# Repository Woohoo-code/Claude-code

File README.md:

# pcba-builder

A CLI that drives the [Claude Code](https://claude.com/claude-code) CLI
(`claude`) to turn a plain-language board description into a first-pass
PCBA (printed circuit board assembly) design package: a bill of materials,
a logical netlist, schematic block descriptions, PCB layout/manufacturing
notes, and assembly/bring-up instructions - plus, generated locally and
offline from that BOM:

- **KiCad export** - real `.kicad_mod` footprints and a placed (unrouted)
  `.kicad_pcb`, with every pin positioned and numbered from its package's
  physical shape and size (JEDEC/IPC-style: pin 1 marked, numbering
  counterclockwise around the body) - see `pinouts.md`.
- **GLB export** - a `.glb` 3D preview of the assembled board (board slab
  + one box per part, sized and placed to match the KiCad layout) you can
  open in any glTF viewer.
- **Online model search** - `pcba-builder models` uses `claude -p` with
  web search to look up a datasheet and, where one exists, a direct
  downloadable 3D/footprint file (STEP/IGES/WRL/GLB) for each part in the
  BOM, and fetches any direct links it finds.
- **Standalone executable** - `scripts/build_exe.sh` / `build_exe.bat`
  package the whole tool with PyInstaller into a single `pcba-builder`
  (or `pcba-builder.exe` on Windows) binary - no Python install needed to
  run it.

It does not draw a schematic or auto-route a board. `export-kicad`
produces a *placed but unrouted* starting point (no ratsnest - the
underlying netlist connectivity from `netlist.md` isn't wired into the
`.kicad_pcb` yet), and `models`/pin-labeling are geometry- and
search-driven, not a guarantee that a given part's silicon pinout matches
the physical positions generated. Always check a generated design against
the real datasheet before fabricating.

## Example boards

Complete, hand-finished design packages in this tool's format. Both are
**placed and fully routed** (0 DRC errors), with Gerbers, pick-and-place,
and a script that regenerates the board through KiCad 7's `pcbnew` API.
`export-kicad`, by contrast, only places parts on a grid.

- [`boards/cc1101-mini/`](boards/cc1101-mini/): an 18.5 x 12.6 mm 4-layer
  TI CC1101 433 MHz module with a U.FL connector.
- [`boards/nano-every-cc1101/`](boards/nano-every-cc1101/): a 70 x 45 mm
  **2-layer** Arduino Nano Every carrier with two CC1101s covering every
  CC1101 band. It has JLCPCB-assembled coil antennas for 315/433/868/915 MHz
  (plus optional SMA jacks), a level shifter, an LDO and a pin breakout.
  Freerouting autoroutes the non-RF nets.

## Requirements

- Python 3.9+ (only to run from source - the packaged executable needs nothing)
- The `claude` CLI installed and authenticated (`claude --version` should work),
  for `build`, `review`, and `models`
- Internet access (through your normal `claude` CLI setup) for `models`

## Install (from source)

```
pip install -e .
```

This installs a `pcba-builder` command. You can also run it directly with
`python -m pcba_builder.cli` from the repo root.

## Build a standalone executable

```
./scripts/build_exe.sh      # Linux/macOS -> dist/pcba-builder
scripts\build_exe.bat       # Windows     -> dist\pcba-builder.exe
```

PyInstaller doesn't cross-compile, so build on the OS you want to run on.
The resulting binary bundles Python and every dependency; it still shells
out to your system's `claude` CLI for `build`/`review`/`models`, so that
still needs to be installed and authenticated separately.

## Usage

```
pcba-builder new boards/led-driver
```

Fills in `boards/led-driver/spec.md` with a template. Edit it to describe
the board: function, connectors/IO, power budget, any parts you already
want to use, and constraints (board size, layer count, cost/quantity).

```
pcba-builder build boards/led-driver
```

Runs `claude -p` against that spec and writes into `boards/led-driver/`:

- `bom.csv` — bill of materials with manufacturer part numbers
- `netlist.md` — nets and connected RefDes.pin lists
- `schematic_blocks.md` — schematic organized by functional block
- `design_notes.md` — layout, stackup, trace-width, EMI, and DFM guidance
- `assembly_instructions.md` — placement order, reflow profile, bring-up checklist

Then, automatically and entirely offline (no `claude` call, deterministic
from `bom.csv`):

- `pinouts.md` — every recognized part's pins, numbered and positioned
  from its package geometry
- `kicad/footprints/*.kicad_mod` and `kicad/<project>.kicad_pcb`
- `<project>.glb` — a 3D preview of the populated board

Re-run just those two exports later (e.g. after hand-editing `bom.csv`)
with `pcba-builder export-kicad boards/led-driver` (regenerates both the
KiCad files and the GLB) or `pcba-builder export-glb boards/led-driver`.

Recognized packages (see `pcba_builder/packages.py` for the authoritative
list): chip passives (0201-2512), SOT-23-3/5/6, SOIC-8/14/16,
TSSOP-8/14/16/20, QFN-16/20/24/32, DIP-8/14/16, TO-220, TO-92, 2.54mm
headers (`HDR-1xN`), and JST-PH connectors. A part whose `Package` field
in `bom.csv` doesn't match gets listed under "Unrecognized packages" in
`pinouts.md` instead of silently dropped.

```
pcba-builder models boards/led-driver
```

Uses `claude -p` with web search to look up each distinct MPN in the BOM
and writes `models/manifest.csv` (MPN, datasheet URL, model URL/format,
source, license note). Any manifest row with a direct link to a
`.step`/`.stp`/`.iges`/`.igs`/`.wrl`/`.glb`/`.gltf` file is then fetched
(size-capped, up to 25 files) into `models/`; everything else is left as
a link in the manifest for you to fetch by hand (e.g. it's behind a
SnapEDA/Ultra Librarian login). Logged to `models/download_log.md`.

```
pcba-builder review boards/led-driver
```

Cross-checks the generated files against each other and against the spec
(e.g. every net references a RefDes that actually exists in the BOM),
flags DFM/DFA risks, and writes `review.md`.

Pass `--model <name>` on any command that calls `claude` to forward it to
`claude --model`.

## How it works

`build`, `review`, and `models` shell out to `claude -p "<prompt>"` with
`--permission-mode acceptEdits` and tool access limited to what each step
needs (`Write Edit Read Glob Grep` for design generation; add
`WebSearch WebFetch` for `models`) — no Bash, scoped to the project
directory, so Claude can only read/write files inside the PCBA project
it's working on and (for `models`) search/fetch web pages.

`export-kicad` and `export-glb` don't call Claude at all: they parse
`bom.csv`, look up each part's package in a small geometry database
(`pcba_builder/packages.py`), lay parts out on a grid, and write the
KiCad and glTF files directly.

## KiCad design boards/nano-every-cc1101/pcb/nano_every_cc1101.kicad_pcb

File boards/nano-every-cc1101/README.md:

# nano-every-cc1101: Arduino Nano Every + 2x CC1101, coil antennas

A compact 70 x 45 mm **2-layer** carrier board for an Arduino Nano Every
with two TI CC1101 radios covering the CC1101's bands (300-348, 387-464
and 779-928 MHz). Each band has its own **coil (helical spring) antenna**,
the kind used in handheld sub-GHz gadgets, so the board no longer needs
room for large printed antennas. All four coils are JLCPCB-assembled; one
0 ohm selector per radio picks the band. The coils are the bent-leg type:
they lie in the board plane and stick out past the right-hand edge, which
is how their makers build them to be mounted.
The Gerbers are generated and pass KiCad DRC with **0 violations, 0
unconnected pads**.

| Top | Bottom (viewed from below) |
|---|---|
|  |  |

## What's on it

| | |
|---|---|
| Board | 70 x 45 x 1.6 mm, 2 layers, FR4 |
| Radio A (U1) | CC1101, 315/433 MHz front end (433 fitted) |
| Radio B (U501) | CC1101, 868/915 MHz front end |
| Antennas | 4 coil antennas AE1-AE4 (433, 315, 868, 915 MHz), each with a T-match for retuning; SMA J1/J2 |
| Host | Arduino Nano Every (ABX00028 + headers, or ABX00033) in sockets S1/S2, USB at the board edge, every pin re-broken-out on J3/J4 |
| Glue | TXS0108E 5 V <-> 3.3 V level shifter, XC6206 3.3 V LDO, power LED |

## Antennas

| Coil | Band | Radio | Part | LCSC | Maker's VSWR at the band centre | Selected as shipped |
|---|---|---|---|---|---|---|
| AE1 | 433 MHz | A | BAT WIRELESS BW433SNX21-5W2 (5 x 21 mm) | C496554 | 1.32 | **yes** (R301 0R) |
| AE2 | 315 MHz | A | BAT WIRELESS BW315SNX39-6W3 (5.45 x 39 mm) | C496553 | 2.49 | fit R311, remove R301, + 315 MHz BOM |
| AE3 | 868 MHz | B | Vollgo VG868SNX18-5W2 (6 x 18 mm) | C718843 | 1.32 | **yes** (R321 0R) |
| AE4 | 915 MHz | B | Vollgo VG915SNX17-5W2 (5 x 17 mm) | C718842 | 1.56 | fit R331, remove R321 |
| J1 / J2 | any | A / B | SMA edge jack (hand-solder, optional) | C496550 | - | fit R403 / R406 |

Radio B's coils are Vollgo parts because the BAT WIRELESS 868 MHz coil
measures VSWR 5.3 in its own datasheet (half the power reflected) and the
915 MHz one 2.6.

Each radio has a short 50 ohm bus; every antenna branch starts with its own
selector right at the bus (so unused branches are only a few mm of line),
then a shunt pad (C3x1) and a series part (L3x1, 0 ohm) at the coil for
retuning with a nanoVNA. The coils are pre-tuned by the maker for their
band; they are not simulated on this board. Frequencies between the coil
bands need a retune of that branch's T-match, or an external antenna on the
SMA jack (quarter-wave whip L = 71 250 / f mm).

Each coil's leg goes through a hole 2 mm from the right edge (1.0 mm for the
0.5 mm wire of the BAT WIRELESS coils, 1.1 mm for the 0.75-0.8 mm Vollgo
wire) and the coil lies in the board's plane beyond the edge, pointing away
from the board: the makers' drawings and JLCPCB's 3D models show exactly
this (the coil is thicker than the board, so it cannot lie on top of it).
Past the edge the 433 MHz coil reaches ~24 mm, the 315 MHz up to ~41 mm,
the 868 MHz ~15 mm and the 915 MHz ~17 mm, so leave room for them in an
enclosure. The 315 MHz coil passes 1.3 mm from the SMA J1 body. All four are
fitted, so the unused coil next to the active one detunes it a little (most
for 868 vs 915, which are close in frequency): check with a nanoVNA and
trim the T-match if you need the last dB.

## Pins (Nano Every)

SPI shared: D13 SCK, D11 MOSI, D12 MISO. Radio A: CSn D10, GDO0 D2, GDO2 D3.
Radio B: CSn D9, GDO0 D4, GDO2 on test pad TP1 (3.3 V).
With RadioLib, e.g. `CC1101 radioA = new Module(10, 2, RADIOLIB_NC, 3);`
and `CC1101 radioB = new Module(9, 4, RADIOLIB_NC);`.

## Firmware

`firmware/dual_cc1101/dual_cc1101.ino` runs both radios at once with
RadioLib (receive on both by interrupt, send / retune from the serial
monitor). Compiled for the Nano Every (arduino:megaavr 1.8.8, RadioLib
7.7.1): **25.7 KB of 48 KB flash (52 %), 1.3 KB of 6 KB RAM (20 %)**, so
there is about 23 KB of flash and 4.8 KB of RAM left for your own code.
The receivers use a 135 kHz filter so two boards' +/-10 ppm crystals
always land inside it (58 kHz gives ~3 dB more range between calibrated
boards).

## Verification

Everything was checked before release (`verify/VERIFICATION.md`, re-run
with `verify/run_all.sh`): DRC 0/0; the netlist rebuilt from the Gerber and
drill files alone (all 73 nets, 0 shorts, 0 opens) with JLCPCB's copper,
drill, annular-ring, solder-mask and paste limits measured on those files;
every pair of parts against JLCPCB's SMD spacing table; every IC pin
against the vendor pin names and the Nano against the ABX00028 datasheet;
every firmware pin traced through the level shifter to its CC1101 pin; the
CPL fitted part by part onto JLCPCB's own footprints (64/64 match,
including which way each coil points); every BOM line against its live
LCSC record (value, package, part number) and stock; the coil, header and
socket holes against the makers' drawings; a 2-D field solver for the
50 ohm lines (49.7-51.4 ohm); a simulation of each antenna feed from the
routed copper (S11 -19 to -35 dB, 97-99 % of the power reaching the coil);
the CC1101 harmonic filters; the power budget.

## Ordering (print ready)

1. PCB: upload `pcb/fab/nano_every_cc1101-gerbers.zip` (**not** the
   fab-package zip, which bundles the Gerber zip with the BOM/CPL and is
   for your records). 8 layers with Protel extensions (.GTL .GBL .GTS .GBS
   .GTP .GTO .GBO .GM1) + one plated drill file. 2 layers, 1.6 mm,
   70 x 45 mm, 1 oz. All standard rules (0.15 mm track/space, 0.25 mm
   minimum drill), no special options.
2. Assembly: `pcb/fab/bom-jlcpcb.csv` + `pcb/fab/cpl-jlcpcb.csv` (top side).
   **Everything except the Nano Every and the optional SMA jacks is
   assembled**: all SMD parts, the four coil antennas, the J3/J4 breakout headers and
   the two 1x15 Nano sockets S1/S2 (Megastar ZX-PM2.54-1-15PY, LCSC
   C7499333, soldered into the Nano's holes). Choose **Economic PCBA**
   (Standard PCBA needs boards of 70 x 70 mm or more); it takes the
   through-hole coils, headers and sockets and needs no rails or fiducials.
   The CPL carries JLCPCB's own footprint angles (checked part by part,
   see `verify/VERIFICATION.md`), so the placement preview should show every
   part on its pads without changes, and all four coils pointing off the
   right edge. Suggested PCBA remark: *"AE1-AE4 are bent-leg spring antennas: leg through the hole, coil lying flat beyond the right board edge, as in the 3D preview."*
   The SMA jacks J1/J2 (C496550) are **not** in the JLCPCB files: JLCPCB lists them as
   Standard PCBA only, which needs a 70 x 70 mm board. They are only needed if
   you move a radio's selector to R403/R406; solder them yourself then (three
   top pads and two bottom ground legs each).
3. The Nano Every ABX00028 comes with its two 1x15 headers **loose** in the
   box; solder them on first. Easiest way to get them straight: push the
   headers (long pins down) into S1/S2 on this board, lay the Nano on top,
   solder the 30 pins on the Nano, then pull it out. Plug it into S1/S2 with
   USB toward the board edge (D12/D13 end at the edge). ABX00033 is the same
   Nano with the headers already soldered. Checked against the ABX00028
   datasheet: 2 x 15 pins, 2.54 mm pitch, rows 15.24 mm apart, 43.18 x
   17.78 mm, same pin order.

## Files

| Path | What |
|---|---|
| `pcb/nano_every_cc1101.kicad_pcb` / `.kicad_pro` / `.kicad_dru` | The routed KiCad 7 board (+ the one custom DRC rule) |
| `pcb/gen_board.py` | Generates the whole board (placement, RF routing, autorouting, pours, silkscreen) |
| `pcb/lib/nano_every_cc1101.pretty` | Coil antenna (edge-overhang) and SMA footprints |
| `pcb/fab_outputs.py`, `pcb/make_fab.sh` | DRC, netlist, BOMs, CPL, Gerbers, renders |
| `pcb/fab/nano_every_cc1101-fab-package.zip` | Everything to order: Gerber zip + both BOMs + CPL |
| `pcb/fab/bom-no-nano.csv` | Purchasing BOM: every part except the Nano Every |
| `pcb/drc_report.txt` | KiCad DRC report |
| `firmware/dual_cc1101/` | Example sketch: both radios with RadioLib |
| `verify/` | Pre-order checks and simulations (`run_all.sh`, `VERIFICATION.md`, results, previews) |
| `antenna/` | v1 printed-antenna study (openEMS), kept for reference |
| `bom.csv`, `netlist.md` | Generated from the board |
| `schematic_blocks.md`, `design_notes.md`, `assembly_instructions.md` | Design docs, bring-up |

## Limits

- Designed, not yet built or measured. Check each coil with a nanoVNA once
  built; the T-match pads are there to retune.
- The coils stick out past the right edge (up to ~41 mm for the 315 MHz
  one), as their makers intend; keep them clear of metal and give them room
  in an enclosure.
- A coil is narrowband (roughly its ISM band); other frequencies need a
  T-match retune or the SMA jack.
- 315 MHz needs radio A's 315 MHz front-end BOM swap (see
  `assembly_instructions.md`).
- No `.kicad_sch` schematic; the netlist is generated from the board.
- Not certified. Radiated use must follow your region's rules.

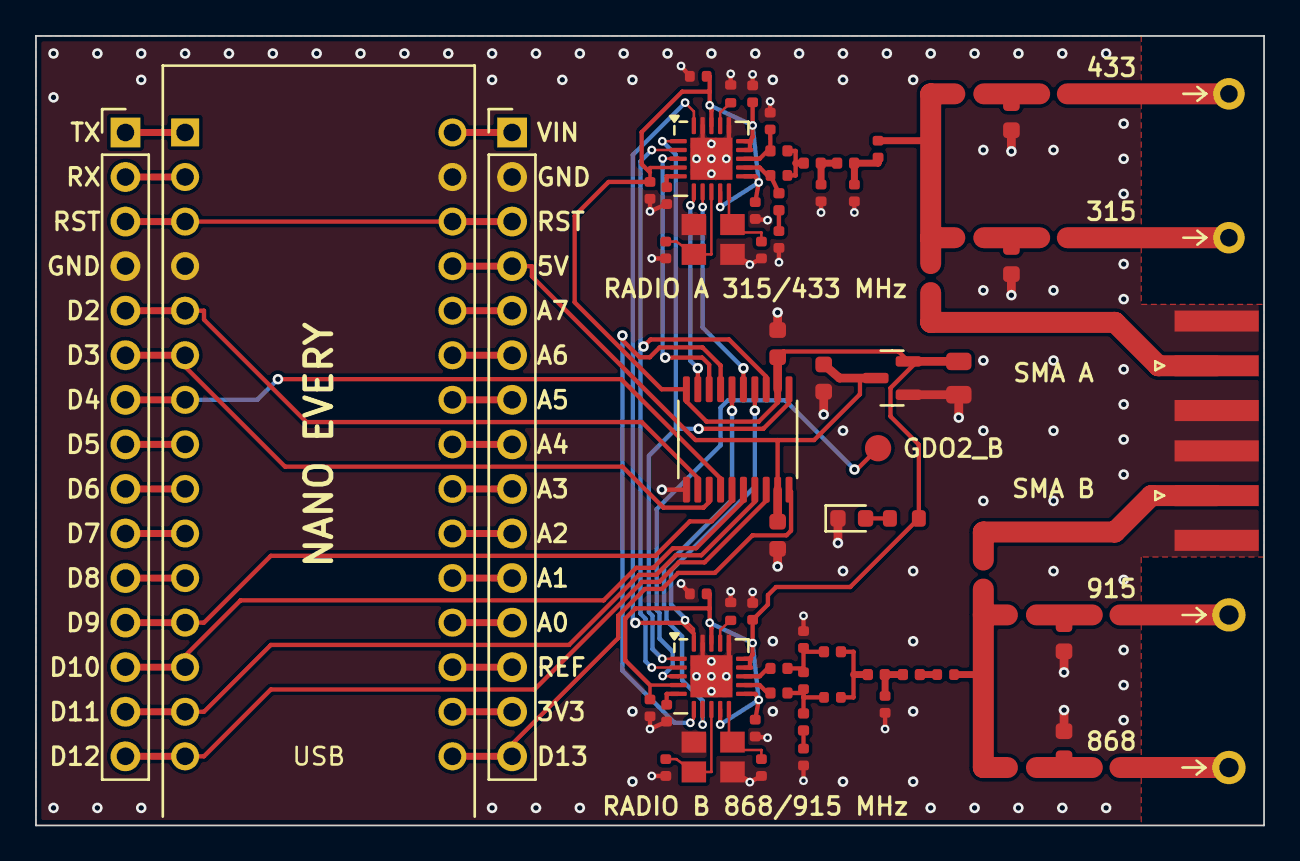
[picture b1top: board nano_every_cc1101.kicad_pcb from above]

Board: 2 copper layers, 70.0 x 45.0 mm, 74 parts (0 on the bottom side), 73 nets.

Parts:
A1: Arduino Nano Every; Arduino_Nano
AE1: BW433SNX21-5W2; Coil_BW433SNX21-5W2_EdgeOverhang
AE2: BW315SNX39-6W3; Coil_BW315SNX39-6W3_EdgeOverhang
AE3: VG868SNX18-5W2; Coil_VG868SNX18-5W2_EdgeOverhang
AE4: VG915SNX17-5W2; Coil_VG915SNX17-5W2_EdgeOverhang
C5: 1uF; C_0603_1608Metric
C6: 10uF; C_0805_2012Metric
C7, C8: 100nF; C_0603_1608Metric
C41, C51, C111, C151, C181, C541, C551, C611, C651, C681: 100nF; C_0402_1005Metric
C81, C101, C581, C601: 27pF; C_0402_1005Metric
C121, C131: 3.9pF; C_0402_1005Metric
C122: 8.2pF; C_0402_1005Metric
C123: 5.6pF; C_0402_1005Metric
C124, C125: 330pF; C_0402_1005Metric
C301, C311, C321, C331: DNP; C_0603_1608Metric
C621: 1.0pF; C_0402_1005Metric
C622, C631: 1.5pF; C_0402_1005Metric
C623: 3.3pF; C_0402_1005Metric
C624: 100pF; C_0402_1005Metric
C625: 12pF; C_0402_1005Metric
D1: red; LED_0603_1608Metric
J1, J2: SMA; SMA_BWSMA-KE-P001_EdgeMount
J3: Breakout 1-15; PinHeader_1x15_P2.54mm_Vertical
J4: Breakout 16-30; PinHeader_1x15_P2.54mm_Vertical
L121, L123, L131: 27nH; L_0402_1005Metric
L122: 22nH; L_0402_1005Metric
L301, L311, L321, L331: 0R; L_0603_1608Metric
L621, L623, L624, L631: 12nH; L_0402_1005Metric
L622, L632: 18nH; L_0402_1005Metric
R1: 1k; R_0603_1608Metric
R171, R671: 56k 1%; R_0402_1005Metric
R301, R321: 0R; R_0603_1608Metric
R311, R331, R403, R406: DNP; R_0603_1608Metric
TP1: GDO2_B; TestPoint_Pad_D1.5mm
U1, U501: CC1101RGPR; Texas_RGP0020H_VQFN-20-1EP_4x4mm_P0.5mm_EP2.4x2.4mm
U2: XC6206P332MR; SOT-23
U3: TXS0108EPWR; TSSOP-20_4.4x6.5mm_P0.65mm
Y1, Y501: 26MHz; Crystal_SMD_3225-4Pin_3.2x2.5mm

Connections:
3V3: C6.2, C7.1, C41.2, C111.2, C151.1, C181.2, C541.2, C611.2, C651.1, C681.2, R1.2, U1.4, U1.9, U1.11, U1.14, U1.15, U1.18, U2.2, U3.2, U3.10, U501.4, U501.9, U501.11, U501.14, U501.15, U501.18
3V3_NANO: A1.17, J4.14
+5V: A1.27, C5.2, C8.2, J4.4, U2.3, U3.19
A0: A1.19, J4.12
A1: A1.20, J4.11
A2: A1.21, J4.10
A3: A1.22, J4.9
A4_SDA: A1.23, J4.8
A5_SCL: A1.24, J4.7
A6: A1.25, J4.6
A7: A1.26, J4.5
ANT_A: C125.2, R301.1, R311.1, R403.2
ANT_B: C625.2, R321.1, R331.1, R406.1
AREF: A1.18, J4.13
CSN_A: U1.7, U3.5
CSN_B: U3.6, U501.7
D0_RX: A1.2, J3.2
D1_TX: A1.1, J3.1
D2: A1.5, J3.5, U3.12
D3: A1.6, J3.6, U3.13
D4: A1.7, J3.7, U3.14
D5: A1.8, J3.8
D6: A1.9, J3.9
D7: A1.10, J3.10
D8: A1.11, J3.11
D9: A1.12, J3.12, U3.15
D10: A1.13, J3.13, U3.16
D11_MOSI: A1.14, J3.14, U3.17
D12_MISO: A1.15, J3.15, U3.18
D13_SCK: A1.16, J4.15, U3.20
DCOUPL_A: C51.2, U1.5
DCOUPL_B: C551.2, U501.5
FEED_315: AE2.1, L311.2
FEED_433: AE1.1, L301.2
FEED_868: AE3.1, L321.2
FEED_915: AE4.1, L331.2
GDO0_A: U1.6, U3.9
GDO0_B: U3.7, U501.6
GDO2_A: U1.3, U3.8
GDO2_B: TP1.1, U501.3
GND: A1.4, A1.29, C5.1, C6.1, C7.2, C8.1, C41.1, C51.1, C81.1, C101.1, C111.1, C122.1, C123.1, C124.1, C131.2, C151.2, C181.1, C301.1, C311.1, C321.2, C331.1, C541.1, C551.1, C581.1, C601.1, C611.1, C623.1, C624.1, C631.2, C651.2, C681.1, D1.1, J1.2, J2.2, J3.4, J4.2, R171.2, R671.2, U1.16, U1.19, U1.21, U2.1, U3.11, U501.16, U501.19, U501.21, Y1.2, Y1.4, Y501.2, Y501.4
LED_A: D1.2, R1.1
M_315: C311.2, L311.1, R311.2
M_433: C301.2, L301.1, R301.2
M_868: C321.1, L321.1, R321.2
M_915: C331.2, L331.1, R331.2
RBIAS_A: R171.1, U1.17
RBIAS_B: R671.1, U501.17
RF_F1_A: C122.2, L122.2, L123.1
RF_F1_B: C623.2, L623.2, L624.1
RF_F2_A: C123.2, C125.1, L123.2
RF_F2_B: C625.1, L624.2
RF_J_A: C121.2, L122.1, L131.2
RF_J_B: C622.2, L623.1, L632.2
RF_L121_A: C124.2, L121.1
RF_L122_B: C624.2, L622.1
RF_N1_B: C621.2, C631.1, L631.2, L632.1
RF_N_A: C131.1, L131.1, U1.13
RF_N_B: L631.1, U501.13
RF_P1_B: C621.1, C622.1, L621.2, L622.2
RF_P_A: C121.1, L121.2, U1.12
RF_P_B: L621.1, U501.12
RST: A1.3, A1.28, J3.3, J4.3
SCLK: U1.1, U3.1, U501.1
SI: U1.20, U3.4, U501.20
SMA_A: J1.1, R403.1
SMA_B: J2.1, R406.2
SO: U1.2, U3.3, U501.2
VIN: A1.30, J4.1
XOSC_Q1_A: C81.2, U1.8, Y1.1
XOSC_Q1_B: C581.2, U501.8, Y501.1
XOSC_Q2_A: C101.2, U1.10, Y1.3
XOSC_Q2_B: C601.2, U501.10, Y501.3

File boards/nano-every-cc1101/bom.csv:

RefDes,Qty,Description,Manufacturer,MPN,Package,Notes
A1,1,Arduino Nano Every ABX00028 (solder its two included 1x15 headers on) or ABX00033 (headers fitted); plugs into S1/S2,Arduino,ABX00028,Arduino_Nano,
AE1,1,"Coil antenna 433 MHz, bent-leg spring 5 x 21 mm (THT, lies off the board edge)",BAT WIRELESS,BW433SNX21-5W2,Coil_THT_EdgeOverhang,LCSC C496554
AE2,1,"Coil antenna 315 MHz, bent-leg spring 5.45 x 39 mm (THT, lies off the board edge)",BAT WIRELESS,BW315SNX39-6W3,Coil_THT_EdgeOverhang,LCSC C496553
AE3,1,"Coil antenna 868 MHz, bent-leg spring 6 x 18 mm (THT, lies off the board edge)",Vollgo,VG868SNX18-5W2,Coil_THT_EdgeOverhang,LCSC C718843
AE4,1,"Coil antenna 915 MHz, bent-leg spring 5 x 17 mm (THT, lies off the board edge)",Vollgo,VG915SNX17-5W2,Coil_THT_EdgeOverhang,LCSC C718842
C5,1,Capacitor 1 uF 10% X5R 0603,Samsung,CL10A105KB8NNNC,C_0603,LCSC C15849
C6,1,Capacitor 10 uF 10% X5R 25 V 0805,Samsung,CL21A106KAYNNNE,C_0805,LCSC C15850
"C7, C8",2,Capacitor 100 nF 10% X7R 50 V 0603,Yageo,CC0603KRX7R9BB104,C_0603,LCSC C14663
"C41, C51, C111, C151, C181, C541, C551, C611, C651, C681",10,Capacitor 100 nF 10% X7R 16 V 0402,Samsung,CL05B104KO5NNNC,C_0402,LCSC C1525
"C81, C101, C581, C601",4,Capacitor 27 pF 5% C0G 0402,FH,0402CG270J500NT,C_0402,LCSC C1557
"C121, C131",2,Capacitor 3.9 pF +/-0.25 pF C0G 0402,Murata,GRM1555C1H3R9CA01D,C_0402,LCSC C85940
C122,1,Capacitor 8.2 pF +/-0.25 pF C0G 0402,Murata,GRM1555C1H8R2CA01D,C_0402,LCSC C76984
C123,1,Capacitor 5.6 pF +/-0.25 pF C0G 0402,Murata,GRM1555C1H5R6CA01D,C_0402,LCSC C85941
"C124, C125",2,Capacitor 330 pF 5% C0G 0402 (DC block / RF bypass),Samsung,CL05C331JB5NNNC,C_0402,LCSC C13533
"C301, C311, C321, C331",4,not fitted (DNP),,,C_0603,leave empty unless re-selecting the antenna
C621,1,Capacitor 1.0 pF +/-0.1 pF C0G 0402,YAGEO,CC0402BRNPO9BN1R0,C_0402,LCSC C309455
"C622, C631",2,Capacitor 1.5 pF +/-0.1 pF C0G 0402,FH,0402CG1R5B500NT,C_0402,LCSC C285112
C623,1,Capacitor 3.3 pF +/-0.1 pF C0G 0402,YAGEO,CC0402BRNPO9BN3R3,C_0402,LCSC C327287
C624,1,Capacitor 100 pF 5% C0G 0402,FH,0402CG101J500NT,C_0402,LCSC C1546
C625,1,Capacitor 12 pF 5% C0G 0402,FH,0402CG120J500NT,C_0402,LCSC C1547
D1,1,LED red 0603,Hubei KENTO Elec,KT-0603R,LED_0603,LCSC C2286
"J1, J2",2,"SMA jack, edge mount (end launch), 50 ohm, 1.6 mm board",BAT WIRELESS,BWSMA-KE-P001,SMA,LCSC C496550
J3,1,"Pin header 1x15 2.54 mm male, straight (breakout)",Megastar,ZX-PZ2.54-1-15PZZ,PinHeader_1x15,LCSC C7501269
J4,1,"Pin header 1x15 2.54 mm male, straight (breakout)",Megastar,ZX-PZ2.54-1-15PZZ,PinHeader_1x15,LCSC C7501269
"L121, L123, L131",3,Inductor 27 nH 5% multilayer 0402,Murata,LQG15HS27NJ02D,L_0402,LCSC C12669
L122,1,Inductor 22 nH 5% multilayer 0402,Murata,LQG15HS22NJ02D,L_0402,LCSC C12670
"L301, L311, L321, L331",4,Jumper 0 ohm 0603,UNI-ROYAL,0603WAF0000T5E,L_0603,LCSC C21189
"L621, L623, L624, L631",4,Inductor 12 nH 2% wire-wound 0402 (868/915 balun),Murata,LQW15AN12NG00D,L_0402,LCSC C86128
"L622, L632",2,Inductor 18 nH 5% wire-wound 0402 (868/915 balun),Murata,LQW15AN18NJ00D,L_0402,LCSC C82917
R1,1,Resistor 1 kohm 1% 0603,UNI-ROYAL,0603WAF1001T5E,R_0603,LCSC C21190
"R171, R671",2,Resistor 56 kohm 1% 0402 (CC1101 RBIAS),UNI-ROYAL,0402WGF5602TCE,R_0402,LCSC C25796
"R301, R321",2,Jumper 0 ohm 0603,UNI-ROYAL,0603WAF0000T5E,R_0603,LCSC C21189
"R311, R331, R403, R406",4,not fitted (DNP),,,R_0603,leave empty unless re-selecting the antenna
"U1, U501",2,"Sub-1 GHz RF transceiver, 300-928 MHz",Texas Instruments,CC1101RGPR,QFN,LCSC C29953
U2,1,LDO 3.3 V 200 mA,Torex,XC6206P332MR-G,SOT-23,LCSC C5446
U3,1,8-bit auto-direction level translator 3.3 V <-> 5 V,Texas Instruments,TXS0108EPWR,TSSOP-20,LCSC C17206
"Y1, Y501",2,Crystal 26 MHz +/-10 ppm CL 16 pF 3225,YXC,X322526MQB4SI,Crystal,LCSC C70573
"S1, S2",2,"Female header 1x15 2.54 mm, 8.5 mm, gold (socket for the Nano Every)",Megastar,ZX-PM2.54-1-15PY,PinSocket_1x15,"LCSC C7499333; soldered into A1's holes, the Nano plugs in"
